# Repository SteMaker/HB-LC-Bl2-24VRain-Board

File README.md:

# HB-LC-Bl2-24VRain-Board
Selbstbau HomeMatic Hardware mit 2 Rolladenaktoren und Anschlussmöglichkeit eines 24V Regensensors

## Überblick
**Achtung: Ich übernehme keinerlei Verantwortung für die Sicherheit und Funktionsfähigkeit der Hardware wie auch der Firmware! Die Hardware verwendet Netzspannung 230V ist deshalb lebensgefährlich!**

Als Firmware verwende ich https://github.com/SteMaker/HB-LC-Bl2-RD.

Die Hardware unterstützt zwei Rolladenaktoren und entspricht im wesentlichen der Arbeit von Jérôme (https://github.com/jp112sdl) an https://github.com/jp112sdl/HM-LC-Bl1-FM-2.

Als Regensensor verwende ich einen Roto 24V Sensor mit Heizung (ich glaube ZEL STG RS 24V). Er bietet nur 3 Anschlussleitungen: 24V, GND, Regenindikation. Keine Möglichkeit die Heizung zu schalten.

Die Anwendung in meinem Fall ist es bis zu 2 Markisen anzusteuern und den in der Nähe befindlichen Regensensor gleich noch mit einzubinden.

## Dankeschön
Ein dickes, fettes Dankeschön an die homematic community sowas zu ermöglichen, insbesondere an pa-pa, Jérôme und Marco.

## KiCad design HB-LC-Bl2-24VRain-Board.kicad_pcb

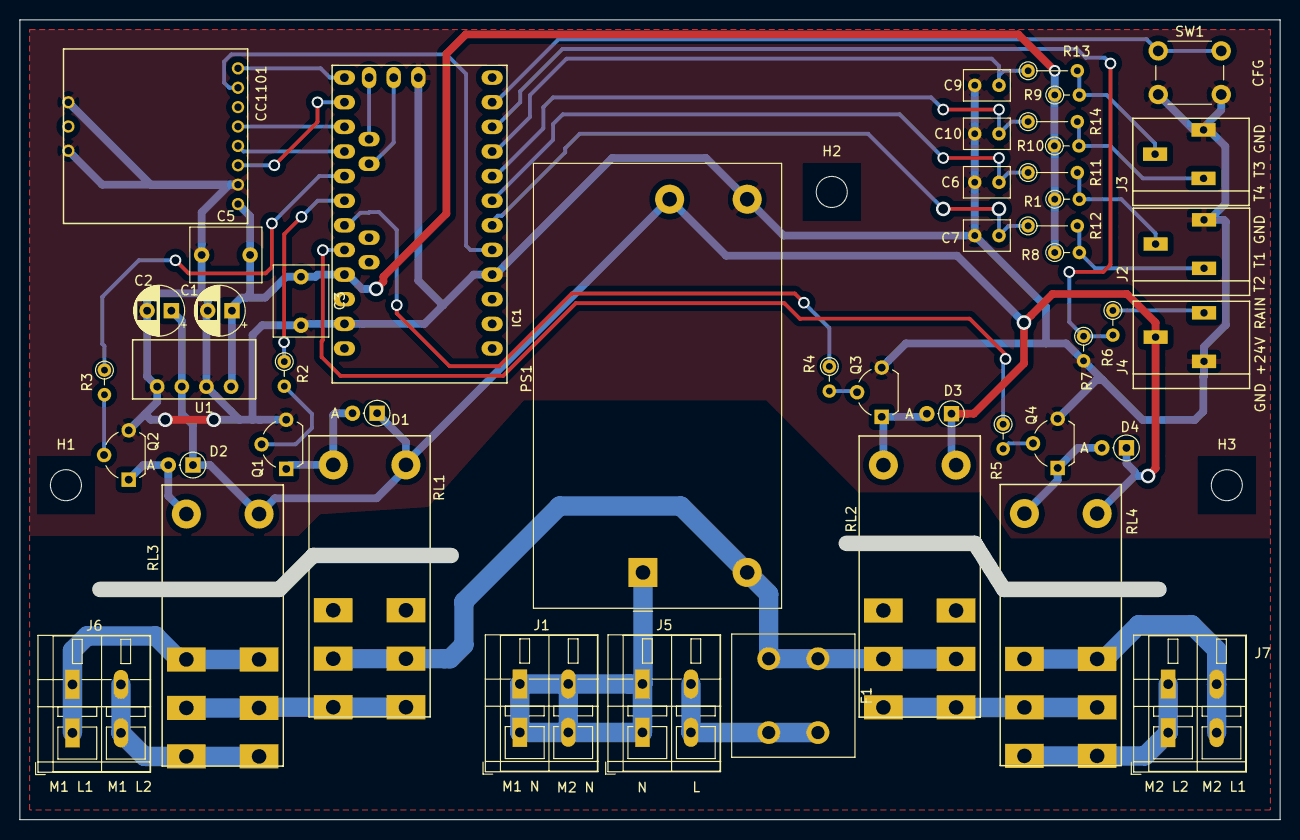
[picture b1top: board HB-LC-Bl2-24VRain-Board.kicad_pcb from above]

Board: 2 copper layers, 128.5 x 81.0 mm, 50 parts (0 on the bottom side), 42 nets.

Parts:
C1, C2: 10µF; CP_Radial_D5.0mm_P2.50mm
C3, C5: 1u; C_Rect_L7.2mm_W5.5mm_P5.00mm_FKS2_FKP2_MKS2_MKP2
C6, C7, C9, C10: 100n; C_Rect_L4.6mm_W3.0mm_P2.50mm_MKS02_FKP02
D1, D2, D3, D4: 1N4148; D_DO-35_SOD27_P2.54mm_Vertical_AnodeUp
F1: Fuse; Fuseholder_Cylinder-5x20mm_Schurter_FPG4_Vertical_Closed
H1, H2, H3: MountingHole; MountingHole_3.2mm_M3
IC1: ArduinoProMini; pro_mini
J1: Motor_N; TerminalBlock_WAGO_236-102_1x02_P5.00mm_45Degree
J2: Taster Markise1; TerminalBlock_WAGO_250-403_1x03_P2.50mm_45Degree
J3: Taster Markise 2; TerminalBlock_WAGO_250-403_1x03_P2.50mm_45Degree
J4: Regensensor; TerminalBlock_WAGO_250-403_1x03_P2.50mm_45Degree
J5: 230V; TerminalBlock_WAGO_236-102_1x02_P5.00mm_45Degree
J6: Motor1; TerminalBlock_WAGO_236-102_1x02_P5.00mm_45Degree
J7: Motor2; TerminalBlock_WAGO_236-102_1x02_P5.00mm_45Degree
PS1: IRM-05-24; Converter_ACDC_MeanWell_IRM-05-xx_THT
Q1, Q2, Q3, Q4: BC337; TO-92L_Wide
R1, R8, R9, R10: 10k; R_Axial_DIN0204_L3.6mm_D1.6mm_P2.54mm_Vertical
R2, R3, R4, R5: 2k4; R_Axial_DIN0204_L3.6mm_D1.6mm_P2.54mm_Vertical
R6: 6k8; R_Axial_DIN0204_L3.6mm_D1.6mm_P2.54mm_Vertical
R7: 1k; R_Axial_DIN0204_L3.6mm_D1.6mm_P2.54mm_Vertical
R11, R12, R13, R14: 47; R_Axial_DIN0204_L3.6mm_D1.6mm_P5.08mm_Vertical
RL1, RL2, RL3, RL4: FINDER-40.61; FIN4061
SW1: SW_Push; SW_PUSH_6mm_H4.3mm
U1: AM1S-2403S; SIL-4
U3: CC1101-868MHz-Module; CC1101_Module

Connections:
+3V3: C1.1, C3.1, C5.2, IC1.21, R1.1, R8.1, R9.1, R10.1, U1.4, U3.1
+24V: C2.1, D1.1, D2.1, D3.1, D4.1, J4.2, PS1.4, RL1.A1, RL2.A1, RL3.A1, RL4.A1, U1.2
/L: F1.2, J5.2
/L_FUSED: F1.1, PS1.2, RL1.11, RL1.21, RL2.11, RL2.21
/M1_DIR: IC1.17, R3.1
/M1_EN: IC1.18, R2.1
/M1_L: RL1.14, RL1.24, RL3.11, RL3.21
/M1_L1: J6.1, RL3.12, RL3.22
/M1_L2: J6.2, RL3.14, RL3.24
/M2_DIR: IC1.20, R5.1
/M2_EN: IC1.19, R4.1
/M2_L: RL2.14, RL2.24, RL4.11, RL4.21
/M2_L1: J7.2, RL4.12, RL4.22
/M2_L2: J7.1, RL4.14, RL4.24
/N: J1.1, J1.2, J5.1, PS1.1
/RAIN: IC1.10, R6.2, R7.1
/RF_CSN: IC1.13, U3.8
/RF_INT: IC1.5, U3.7
/RF_MISO: IC1.15, U3.5
/RF_MOSI: IC1.14, U3.3
/RF_SCLK: IC1.16, U3.4
/TA1: C6.1, IC1.7, R11.1
/TA1_IN: J2.2, R1.2, R11.2
/TA2: C7.1, IC1.6, R12.1
/TA2_IN: J2.1, R8.2, R12.2
/TA3: C9.1, IC1.9, R13.1
/TA3_IN: J3.2, R9.2, R13.2
/TA4: C10.1, IC1.8, R14.1
/TA4_IN: J3.1, R10.2, R14.2
GND: C1.2, C2.2, C3.2, C5.1, C6.2, C7.2, C9.2, C10.2, IC1.4, IC1.23, IC1.29, J2.3, J3.3, J4.1, PS1.3, Q1.3, Q2.3, Q3.3, Q4.3, R7.2, SW1.2, U1.1, U1.3, U3.2, U3.10, U3.11
unnamed: D1.2, Q1.1, RL1.A2
unnamed: D2.2, Q2.1, RL3.A2
unnamed: D3.2, Q3.1, RL2.A2
unnamed: D4.2, Q4.1, RL4.A2
unnamed: IC1.11, SW1.1
unnamed: J4.3, R6.1
unnamed: Q1.2, R2.2
unnamed: Q2.2, R3.2
unnamed: Q3.2, R4.2
unnamed: Q4.2, R5.2
unnamed: RL1.12, RL1.22
unnamed: RL2.12, RL2.22

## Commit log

2019-11-09 Added creative-commons license
2019-11-09 Initial commit - version 0.9
2019-11-12 Several schematic updates
2019-11-13 Few updates to layout. But not yet done.
2019-11-13 Version 1.0
    - Some beautifications done
    - Replaced 2x100nF at CC1101 at Arduino woth 1uF each
    - Fixed the base resistor for the relay control
2019-11-13 Added schematic and layouts as pdf
2019-11-14 Adding BOM, not finished
2019-11-14 Added the BOM to a new file
2020-04-05 Added missing GND connections of CC101
